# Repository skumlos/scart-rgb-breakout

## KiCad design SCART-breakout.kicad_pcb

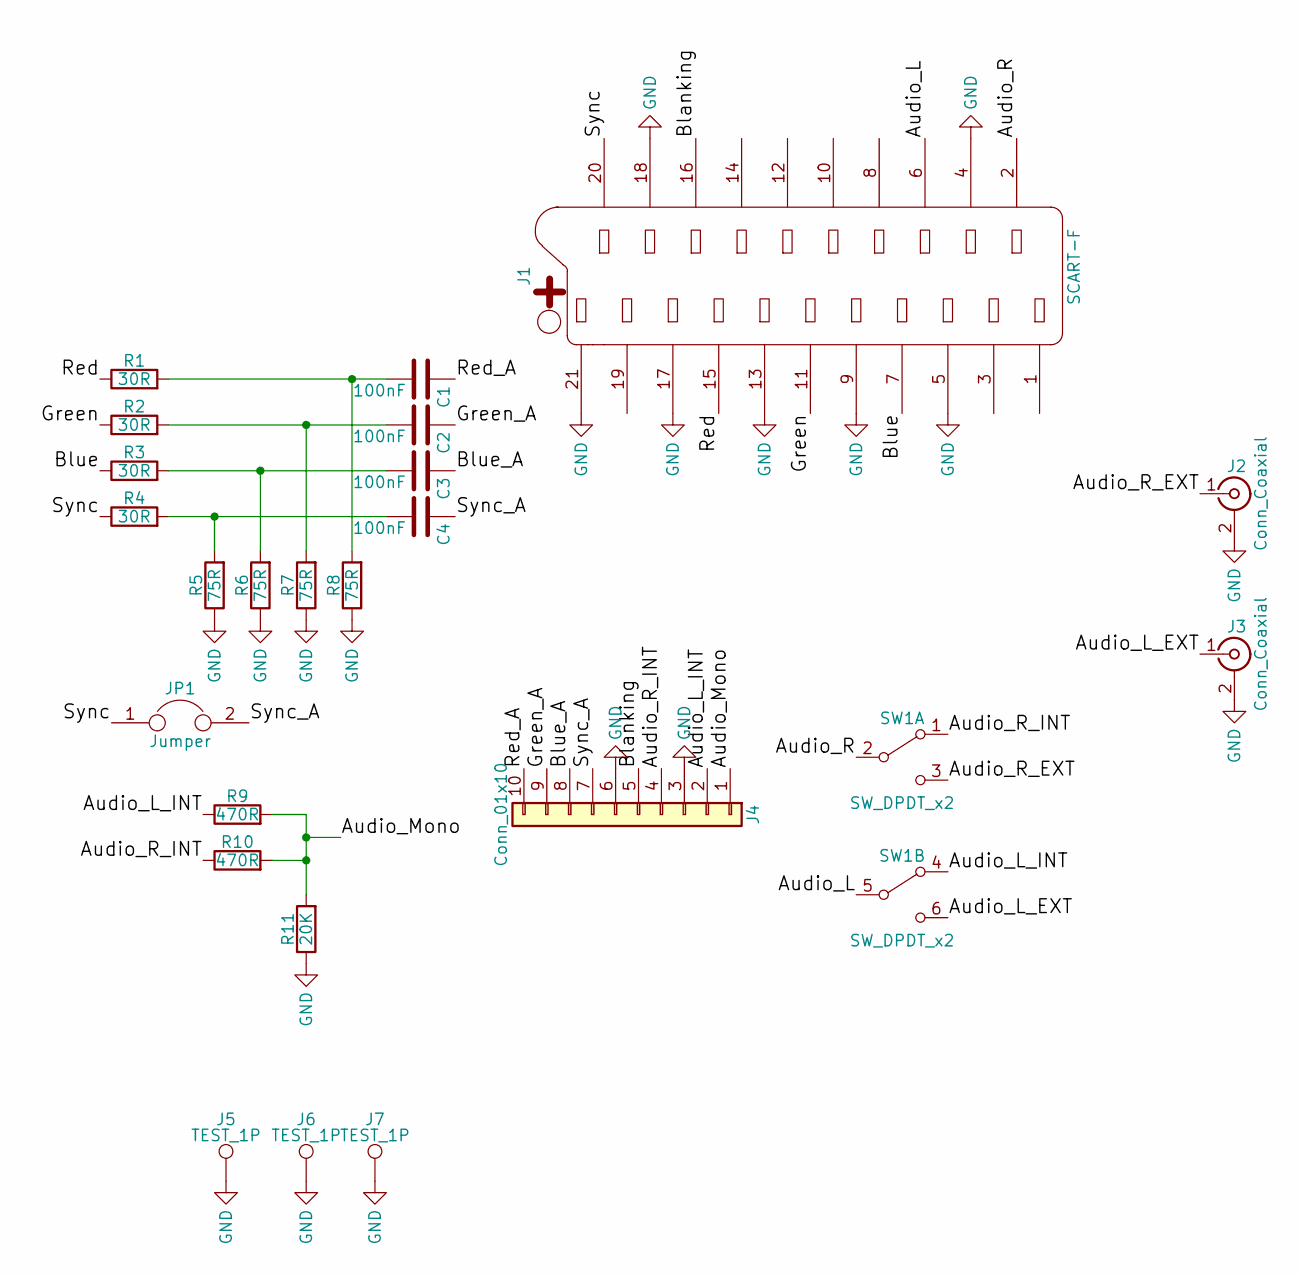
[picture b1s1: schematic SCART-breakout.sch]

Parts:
C1, C2, C3, C4: 100nF; C_0805
J1: SCART-F; K-SCARTX-024
J2, J3: Conn_Coaxial; RCJ-02
J4: Conn_01x10; Pin_Header_Angled_1x10_Pitch2.54mm
J5, J6, J7: TEST_1P; MountingHole_3.2mm_M3_DIN965_Pad
JP1: Jumper; GS2
R1, R2, R3, R4: 30R; R_0805
R5, R6, R7, R8: 75R; R_0805
R9, R10: 470R; R_0805
R11: 20K; R_0805
SW1: SW_DPDT_x2; eswitch-dpdt-m2

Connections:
/Audio_L: J1.6, SW1.5 (B)
/Audio_L_EXT: J3.1 (In), SW1.6 (C)
/Audio_L_INT: J4.2, R9.1, SW1.4 (A)
/Audio_Mono: J4.1, R9.2, R10.2, R11.2
/Audio_R: J1.2, SW1.2 (B)
/Audio_R_EXT: J2.1 (In), SW1.3 (C)
/Audio_R_INT: J4.4, R10.1, SW1.1 (A)
/Blanking: J1.16, J4.5
/Blue: J1.7, R3.1
/Blue_A: C3.1, J4.8
/Green: J1.11, R2.1
/Green_A: C2.1, J4.9
/Red: J1.15, R1.1
/Red_A: C1.1, J4.10
/Sync: J1.20, JP1.1, R4.1
/Sync_A: C4.1, J4.7, JP1.2
GND: J1.4, J1.5, J1.9, J1.13, J1.17, J1.18, J1.21, J2.2 (Ext), J3.2 (Ext), J4.3, J4.6, J5.1, J6.1, J7.1, R5.1, R6.1, R7.1, R8.1, R11.1
unnamed: C1.2, R1.2, R8.2
unnamed: C2.2, R2.2, R7.2
unnamed: C3.2, R3.2, R6.2
unnamed: C4.2, R4.2, R5.2

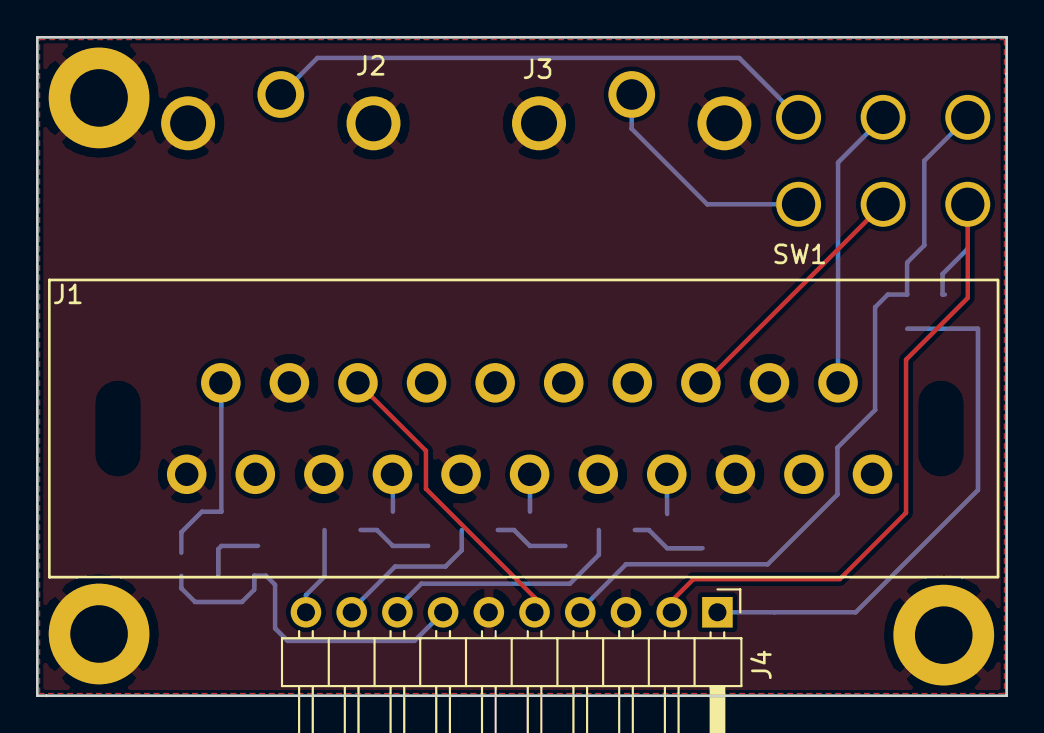
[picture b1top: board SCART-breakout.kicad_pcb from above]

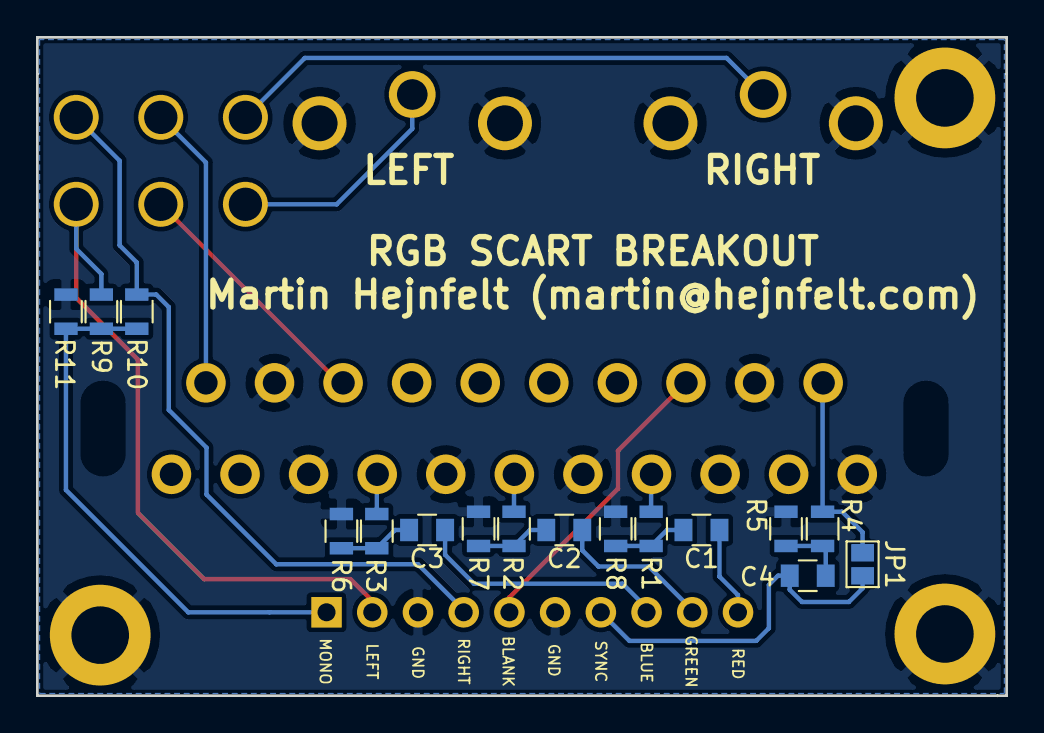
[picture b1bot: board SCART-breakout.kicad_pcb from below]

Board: 2 copper layers, 53.8 x 36.6 mm, 24 parts (16 on the bottom side), 21 nets.
